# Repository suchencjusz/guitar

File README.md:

# guitar
My attempts on guitar effects! :D

### tremolo
Actually, the hardest parts were my first encounter with LTspice, and to be precise with ideal mathematical simulations;
as it turns out, building such a circuit with real components doesn't guarantee that it will actually work!
The next reality check came when I tried etching a PCB at home using sodium persulfate, the board turned out fine, but I'm not sure I'd take on that grueling manual task again if I were working with THT components.
The problem with my board was this: there was no ground-plane... It worked, but it picked up noise like the eye of Moscow in Pripyat... Oh, and on top of that, I placed the components incorrectly in KiCad.
I learned more about signal integrity on PCBs and how to do it better, so I redesigned the board and ordered it from a Chinese manufacturer.
After soldering, it worked right away it's never worked this well before. I think I've really learned my lesson about signal integrity on PCBs... the sound is crystal clear.

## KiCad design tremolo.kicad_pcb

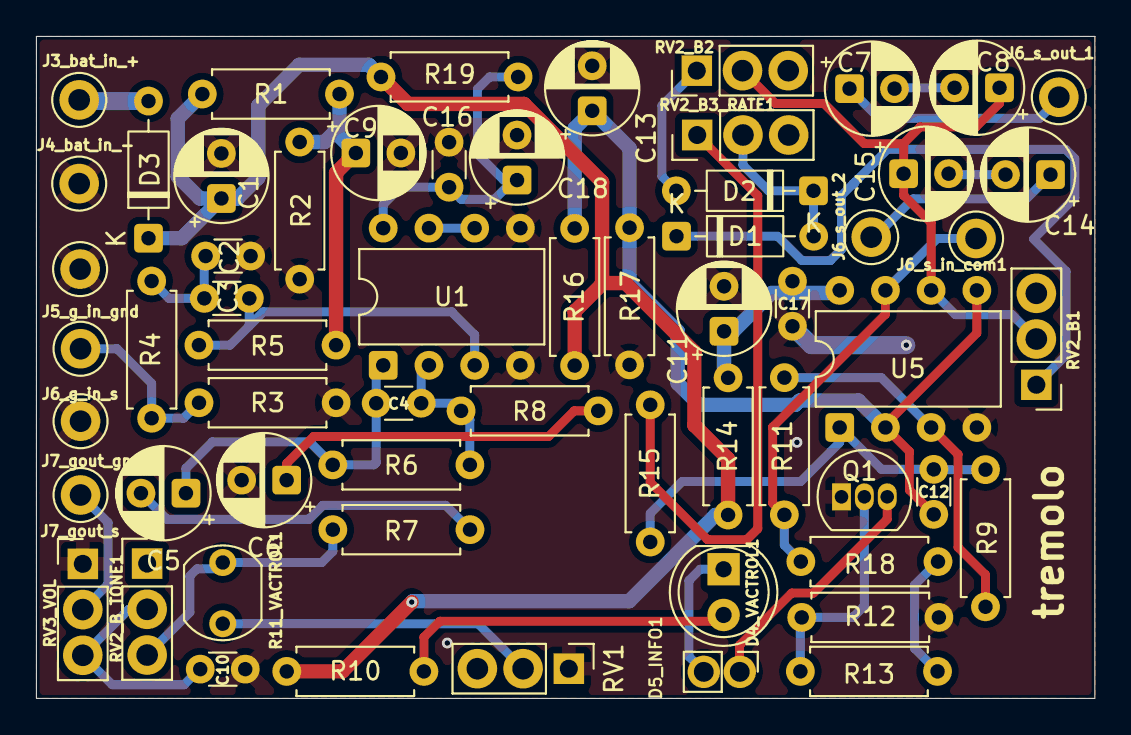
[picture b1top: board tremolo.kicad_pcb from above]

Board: 2 copper layers, 58.8 x 36.8 mm, 61 parts (0 on the bottom side), 36 nets.

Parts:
C1: 100u; CP_Radial_D5.0mm_P2.50mm
C2, C4, C12: 100p; C_Disc_D3.0mm_W1.6mm_P2.50mm
C3: 47n; C_Disc_D3.0mm_W1.6mm_P2.50mm
C5, C11, C18: 2.2u; CP_Radial_D5.0mm_P2.50mm
C6: 4.7u; CP_Radial_D5.0mm_P2.50mm
C7, C8: 10u; CP_Radial_D5.0mm_P2.50mm
C9, C13: 47u; CP_Radial_D5.0mm_P2.50mm
C10: 22n; C_Disc_D3.0mm_W1.6mm_P2.50mm
C14, C15: 1u; CP_Radial_D5.0mm_P2.50mm
C16, C17: 100n; C_Disc_D3.0mm_W1.6mm_P2.50mm
D1, D2, D3: 1N914; D_DO-35_SOD27_P7.62mm_Horizontal
D4_VACTROL1: LED; LED_D5.0mm
D5_INFO1: LED; PinHeader_1x02_P2.00mm_Vertical
J3_bat_in_+, J4_bat_in_-, J5_g_in_gnd, J6_g_in_s, J6_s_in_com1, J6_s_out_1, J6_s_out_2, J7_gout_gnd, J7_gout_s: Conn_01x01_Pin; TestPoint_Loop_D2.50mm_Drill1.0mm
Q1: 2N3904; TO-92_Inline
R1, R2, R8, R13, R16, R17: 10k; R_Axial_DIN0207_L6.3mm_D2.5mm_P7.62mm_Horizontal
R3, R5: 1Meg; R_Axial_DIN0207_L6.3mm_D2.5mm_P7.62mm_Horizontal
R4: 1k; R_Axial_DIN0207_L6.3mm_D2.5mm_P7.62mm_Horizontal
R6: 33k; R_Axial_DIN0207_L6.3mm_D2.5mm_P7.62mm_Horizontal
R7, R11: 100k; R_Axial_DIN0207_L6.3mm_D2.5mm_P7.62mm_Horizontal
R9: 220k; R_Axial_DIN0207_L6.3mm_D2.5mm_P7.62mm_Horizontal
R10: 330; R_Axial_DIN0207_L6.3mm_D2.5mm_P7.62mm_Horizontal
R11_VACTROL1: R_Photo; R_LDR_5.1x4.3mm_P3.4mm_Vertical
R12: 3.3k; R_Axial_DIN0207_L6.3mm_D2.5mm_P7.62mm_Horizontal
R14, R19: 100; R_Axial_DIN0207_L6.3mm_D2.5mm_P7.62mm_Horizontal
R15: 33.3k; R_Axial_DIN0207_L6.3mm_D2.5mm_P7.62mm_Horizontal
R18: 4.7k; R_Axial_DIN0207_L6.3mm_D2.5mm_P7.62mm_Horizontal
RV1, RV2_B1, RV2_B2, RV2_B_TONE1: 100k; PinHeader_1x03_P2.54mm_Vertical
RV2_B3_RATE1: 1Meg; PinHeader_1x03_P2.54mm_Vertical
RV3_VOL: 250k; PinHeader_1x03_P2.54mm_Vertical
U1: TL062CP; DIP-8_W7.62mm
U5: LM358P; DIP-8_W7.62mm

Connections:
/4.5V: C9.1, R1.2, R2.1, R5.2
/9V: C1.1, D3.1 (K), R1.1, R10.2, R14.1, R16.2, R19.2
/AUDIO: R7.2, R11_VACTROL1.1, RV2_B_TONE1.3
/GND: C1.2, C2.1, C6.2, C9.2, C10.2, C11.2, C13.2, C16.1, C17.1, C18.2, J4_bat_in_-.1 (Pin_1_1), J5_g_in_gnd.1 (Pin_1_1), J7_gout_gnd.1 (Pin_1_1), Q1.1 (E), R2.2, R3.2, R12.2, R17.2, RV1.1, RV3_VOL.1, U1.4 (VCC-), U1.5 (2IN+), U5.4 (GND)
unnamed: C2.2, C3.2, R4.1
unnamed: C5.2, R7.1
unnamed: C6.1, R8.2
unnamed: C7.2, C8.2
unnamed: C10.1, RV2_B_TONE1.2, RV3_VOL.3
unnamed: C14.2, C15.2
unnamed: D1.2 (A), D2.1 (K), RV2_B3_RATE1.2
unnamed: D1.1 (K), RV2_B1.1
unnamed: D2.2 (A), RV2_B2.1
unnamed: D3.2 (A), J3_bat_in_+.1 (Pin_1_1)
unnamed: D4_VACTROL1.2 (A), R10.1
unnamed: D4_VACTROL1.1 (K), D5_INFO1.2 (A)
unnamed: D5_INFO1.1 (K), Q1.3 (C)
unnamed: J6_g_in_s.1 (Pin_1_1), R3.1, R4.2
unnamed: J6_s_in_com1.1 (Pin_1_1), R11.1, R18.2, U5.7 (2OUT)
unnamed: C7.1, J6_s_out_1.1 (Pin_1_1)
unnamed: C14.1, J6_s_out_2.1 (Pin_1_1)
unnamed: J7_gout_s.1 (Pin_1_1), RV3_VOL.2
unnamed: Q1.2 (B), R12.1, R13.1
unnamed: R11_VACTROL1.2, RV1.2
unnamed: R13.2, R18.1
unnamed: R15.1, RV2_B3_RATE1.1
unnamed: C3.1, R5.1, U1.3 (1IN+)
unnamed: C4.2, R6.2, R8.1, U1.2 (1IN-)
unnamed: C4.1, C5.1, R6.1, U1.1 (1OUT)
unnamed: U1.6 (2IN-), U1.7 (2OUT)
unnamed: C16.2, C18.1, R19.1, U1.8 (VCC+)
unnamed: R9.2, R11.2, U5.3 (1IN+)
unnamed: C12.1, C13.1, R16.1, R17.1, U5.2 (1IN-), U5.5 (2IN+)
unnamed: C12.2, R9.1, R15.2, U5.1 (1OUT)
unnamed: C8.1, C15.1, RV2_B1.2, RV2_B2.2, U5.6 (2IN-)
unnamed: C11.1, C17.2, R14.2, U5.8 (VCC)
